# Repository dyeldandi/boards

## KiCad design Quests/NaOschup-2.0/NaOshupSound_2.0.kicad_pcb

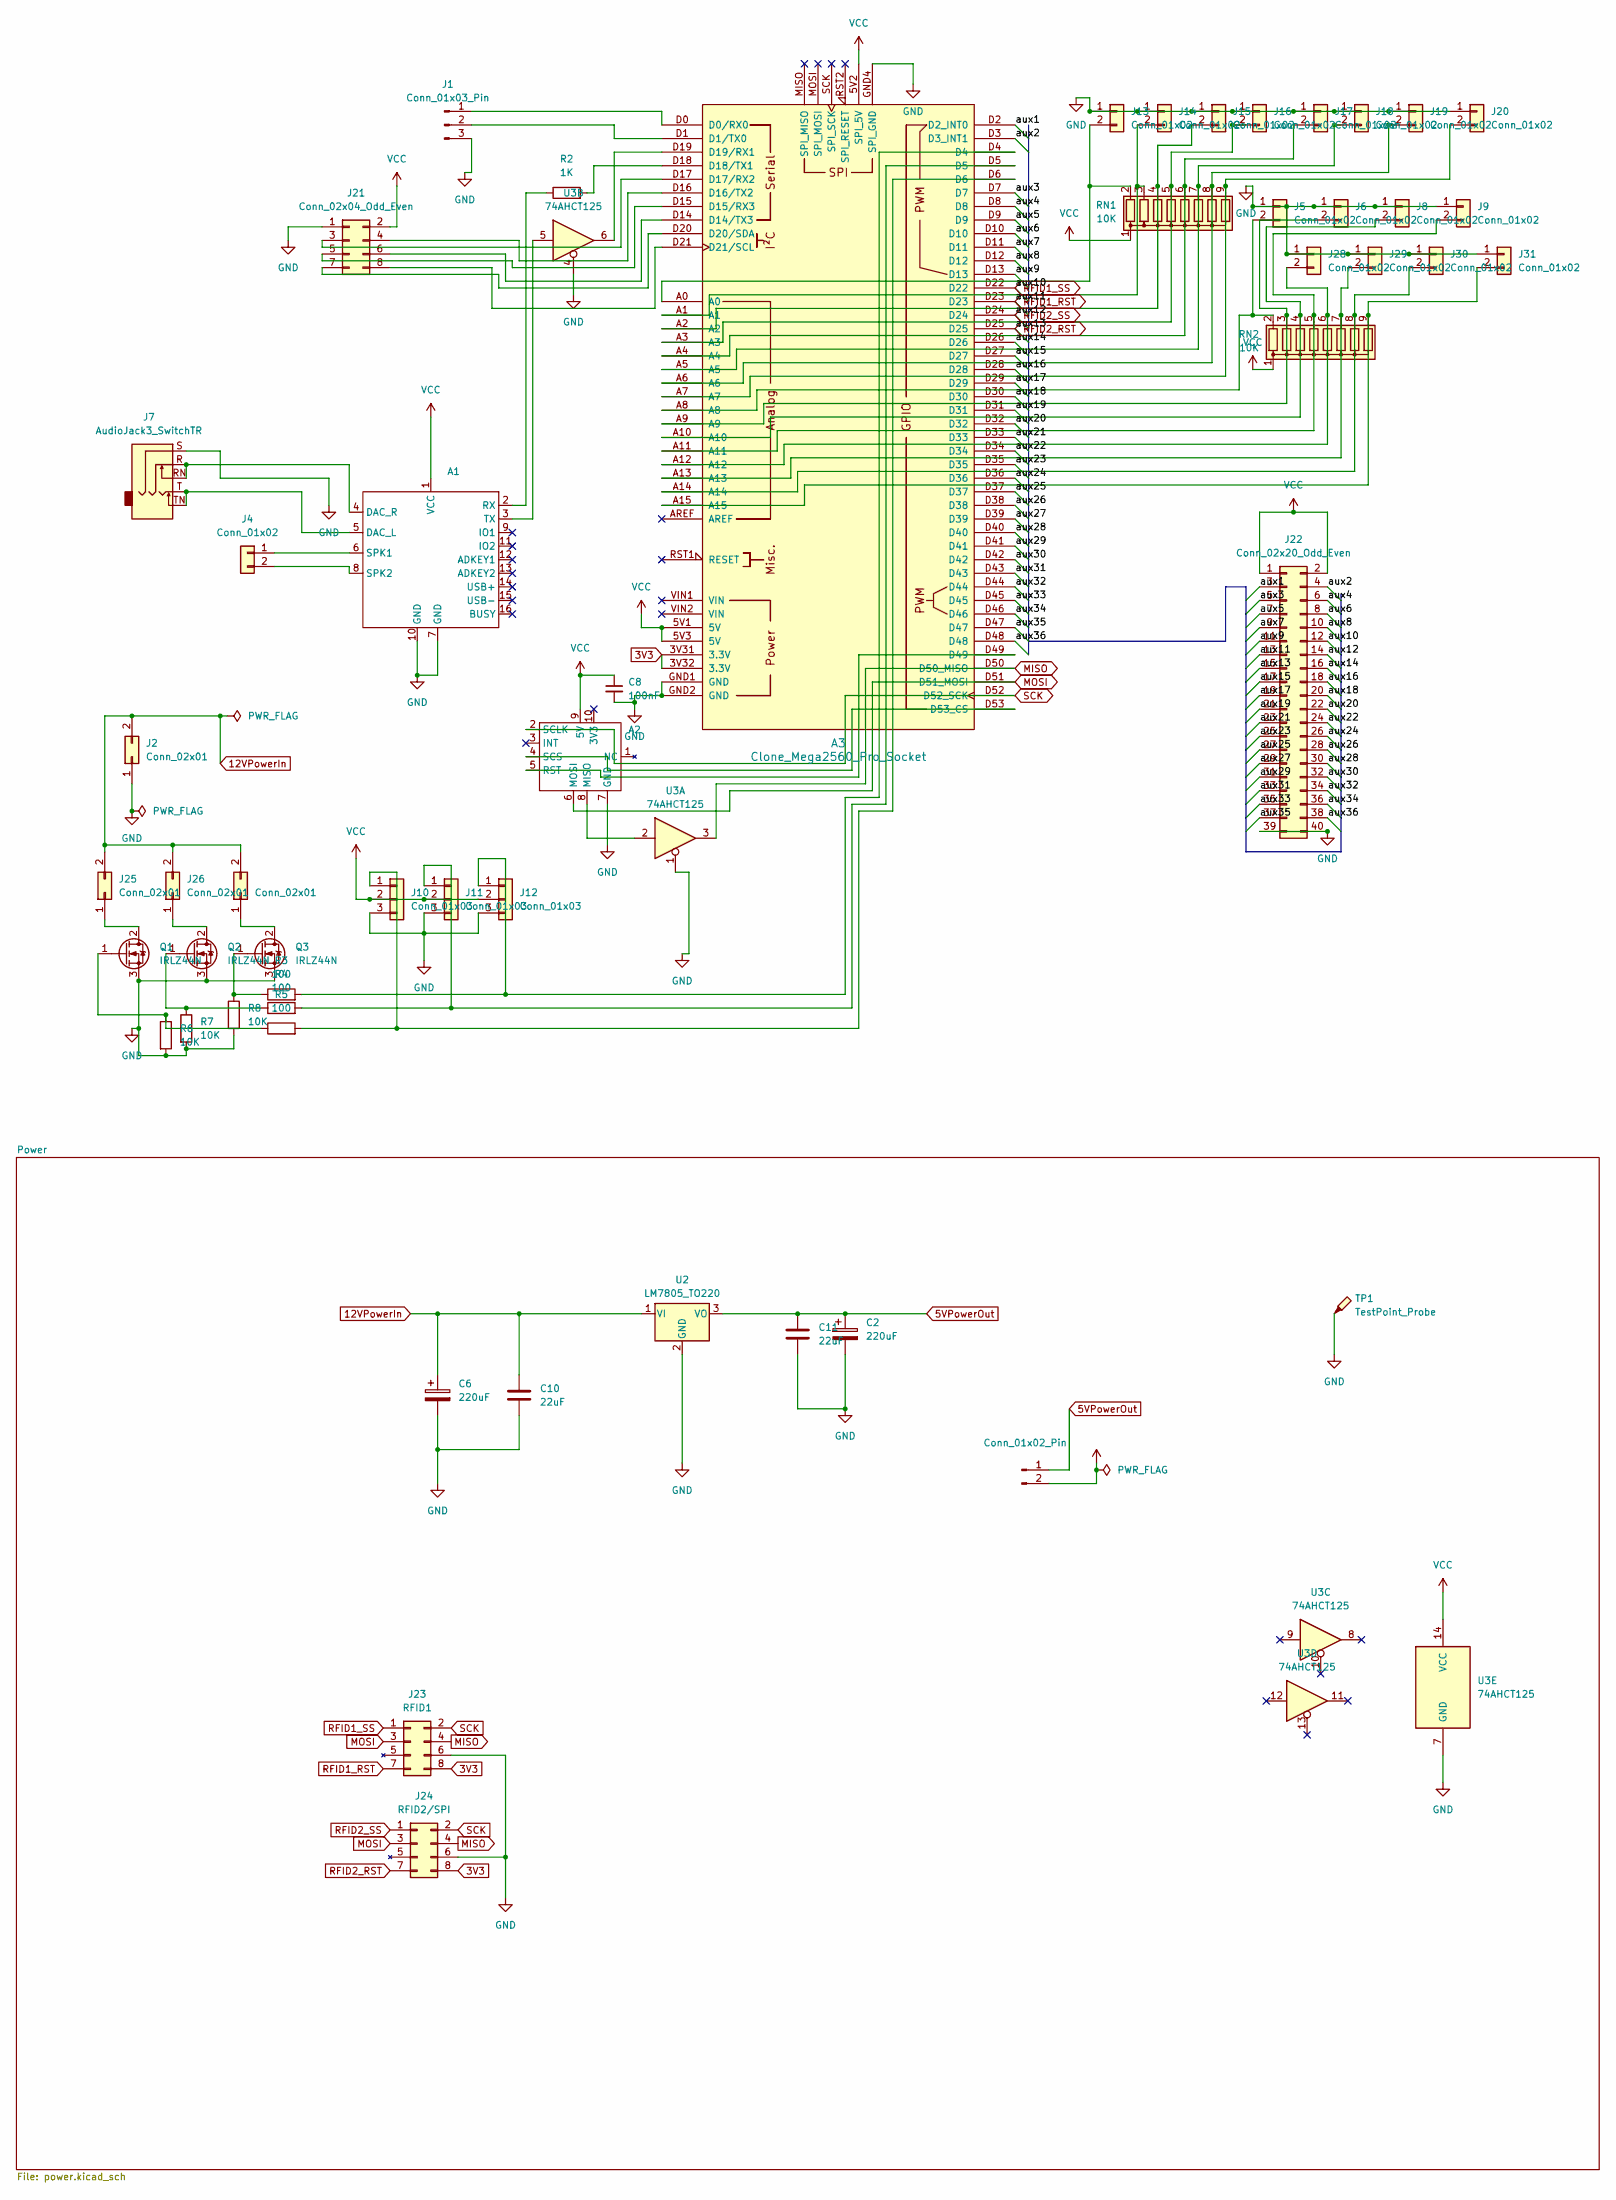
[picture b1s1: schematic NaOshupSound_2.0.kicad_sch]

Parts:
A1: DFPLayerMini
A2: W5500Module
A3: Clone_Mega2560_Pro_Socket
C2, C6: 220uF; CP_Radial_D6.3mm_P2.50mm
C8: 100nF; C_0805_2012Metric_Pad1.18x1.45mm_HandSolder
C10, C11: 22uF; C_1206_3216Metric
J1: Conn_01x03_Pin; FanPinHeader_1x03_P2.54mm_Vertical
J2, J25, J26, J27: Conn_02x01; Molex_Mini-Fit_Jr_5569-02A2_2x01_P4.20mm_Horizontal_Hanging
J3: Conn_01x02_Pin; PinHeader_1x02_P2.54mm_Vertical
J4: Conn_01x02; Connector_Connfly_P2.54_2P
J5, J6, J8, J9, J13, J14, J15, J16, J17, J18, J19, J20, J28, J29, J30, J31: Conn_01x02; Connector_Connfly_P2.54_2P_R
J7: AudioJack3_SwitchTR; Jack_3.5mm_CUI_SJ1-3525N_Horizontal
J10, J11, J12: Conn_01x03; PinSocket_1x03_P2.54mm_Vertical
J21: Conn_02x04_Odd_Even; IDC-Header_2x04_P2.54mm_Vertical
J22: Conn_02x20_Odd_Even; IDC-Header_2x20_P2.54mm_Vertical
J23: RFID1; IDC-Header_2x04_P2.54mm_Vertical
J24: RFID2/SPI; IDC-Header_2x04_P2.54mm_Vertical
Q1, Q2, Q3: IRLZ44N; TO-220-3_Vertical
R2: 1K; R_0805_2012Metric_Pad1.20x1.40mm_HandSolder
R3, R4, R5: 100; R_0805_2012Metric_Pad1.20x1.40mm_HandSolder
R6, R7, R8: 10K; R_0805_2012Metric_Pad1.20x1.40mm_HandSolder
RN1, RN2: 10K; R_Array_SIP9
TP1: TestPoint_Probe; PinHeader_1x01_P2.54mm_Vertical
U2: LM7805_TO220; TO-220-3_Vertical
U3: 74AHCT125; SOIC-14_3.9x8.7mm_P1.27mm

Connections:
3V3: A3.3V31 (3.3V), A3.3V32 (3.3V), J23.8 (VCC_3V3), J24.8 (VCC_3V3)
5VPowerOut: C2.1, C11.1, J3.1, U2.3 (VO)
12VPowerIn: C6.1, C10.1, J2.2, J25.2, J26.2, J27.2, U2.1 (VI)
/aux1: A3.D2 (D2_INT0), J22.3
/aux2: A3.D3 (D3_INT1), J22.4
/aux3: A3.D7, J22.5
/aux4: A3.D8, J22.6
/aux5: A3.D9, J22.7
/aux6: A3.D10, J22.8
/aux7: A3.D11, J22.9
/aux8: A3.D12, J22.10
/aux9: A3.D13, J22.11
/aux14: A3.D26, J22.16
/aux15: A3.D27, J22.17
/aux16: A3.D28, J22.18
/aux17: A3.D29, J22.19
/aux18: A3.D30, J22.20
/aux19: A3.D31, J22.21
/aux20: A3.D32, J22.22
/aux21: A3.D33, J22.23
/aux22: A3.D34, J22.24
/aux23: A3.D35, J22.25
/aux24: A3.D36, J22.26
/aux25: A3.D37, J22.27
/aux26: A3.D38, J22.28
/aux27: A3.D39, J22.29
/aux28: A3.D40, J22.30
/aux29: A3.D41, J22.31
/aux30: A3.D42, J22.32
/aux31: A3.D43, J22.33
/aux32: A3.D44, J22.34
/aux33: A3.D45, J22.35
/aux34: A3.D46, J22.36
/aux35: A3.D47, J22.37
/aux36: A3.D48, J22.38
GND: A1.7 (GND), A1.10 (GND), A2.7 (GND), A3.GND1 (GND), A3.GND2 (GND), A3.GND4 (SPI_GND), C2.2, C6.2, C8.2, C10.2, C11.2, J1.3, J2.1, J5.1, J6.1, J7.S, J8.1, J9.1, J10.3, J11.3, J12.3, J13.1, J14.1, J15.1, J16.1, J17.1, J18.1, J19.1, J20.1, J21.1, J22.39, J22.40, J23.6 (GND), J24.6 (GND), J28.1, J29.1, J30.1, J31.1, Q1.3 (S), Q2.3 (S), Q3.3 (S), R6.2, R7.2, R8.2, TP1.1, U2.2 (GND), U3.1, U3.4, U3.7 (GND)
MISO: A3.D50 (D50_MISO), J23.4 (MISO), J24.4 (MISO), U3.3
MOSI: A2.6 (MOSI), A3.D51 (D51_MOSI), J23.3 (MOSI), J24.3 (MOSI)
unnamed: A1.5 (DAC_L), J7.T, J7.TN
unnamed: A1.4 (DAC_R), J7.R, J7.RN
unnamed: A1.2 (RX), R2.1
unnamed: A1.6 (SPK1), J4.1
unnamed: A1.8 (SPK2), J4.2
unnamed: A1.3 (TX), U3.5
unnamed: A2.8 (MISO), U3.2
unnamed: A2.5 (RST), A3.D49
unnamed: A2.4 (SCS), A3.D53 (D53_CS)
unnamed: A3.D0 (D0/RX0), J1.1
unnamed: A3.D1 (D1/TX0), J1.2
unnamed: A3.D14 (D14/TX3), J21.6
unnamed: A3.D15 (D15/RX3), J21.5
unnamed: A3.D16 (D16/TX2), J21.4
unnamed: A3.D17 (D17/RX2), J21.3
unnamed: A3.D18 (D18/TX1), R2.2
unnamed: A3.D19 (D19/RX1), U3.6
unnamed: A3.D20 (D20/SDA), J21.7
unnamed: A3.D21 (D21/SCL), J21.8
unnamed: A3.A8, J5.2, RN2.2 (R1)
unnamed: A3.A9, J6.2, RN2.3 (R2)
unnamed: A3.A10, J8.2, RN2.4 (R3)
unnamed: A3.A11, J9.2, RN2.5 (R4)
unnamed: A3.D6, J10.1, R5.2
unnamed: A3.D5, J11.1, R4.2
unnamed: A3.D4, J12.1, R3.2
unnamed: A3.A0, J13.2, RN1.2 (R1)
unnamed: A3.A1, J14.2, RN1.3 (R2)
unnamed: A3.A2, J15.2, RN1.4 (R3)
unnamed: A3.A3, J16.2, RN1.5 (R4)
unnamed: A3.A4, J17.2, RN1.6 (R5)
unnamed: A3.A5, J18.2, RN1.7 (R6)
unnamed: A3.A6, J19.2, RN1.8 (R7)
unnamed: A3.A7, J20.2, RN1.9 (R8)
unnamed: J25.1, Q1.2 (D)
unnamed: J26.1, Q2.2 (D)
unnamed: J27.1, Q3.2 (D)
unnamed: A3.A12, J28.2, RN2.6 (R5)
unnamed: A3.A13, J29.2, RN2.7 (R6)
unnamed: A3.A14, J30.2, RN2.8 (R7)
unnamed: A3.A15, J31.2, RN2.9 (R8)
unnamed: Q1.1 (G), R5.1, R6.1
unnamed: Q2.1 (G), R4.1, R7.1
unnamed: Q3.1 (G), R3.1, R8.1
RFID1_RST: A3.D23, J22.13, J23.7 (RST)
RFID1_SS: A3.D22, J22.12, J23.1 (SS)
RFID2_RST: A3.D25, J22.15, J24.7 (RST)
RFID2_SS: A3.D24, J22.14, J24.1 (SS)
SCK: A2.2 (SCLK), A3.D52 (D52_SCK), J23.2 (SCK), J24.2 (SCK)
VCC: A1.1 (VCC), A2.9 (5V), A3.5V1 (5V), A3.5V2 (SPI_5V), A3.5V3 (5V), C8.1, J3.2, J10.2, J11.2, J12.2, J21.2, J22.1, J22.2, RN1.1 (common), RN2.1 (common), U3.14 (VCC)

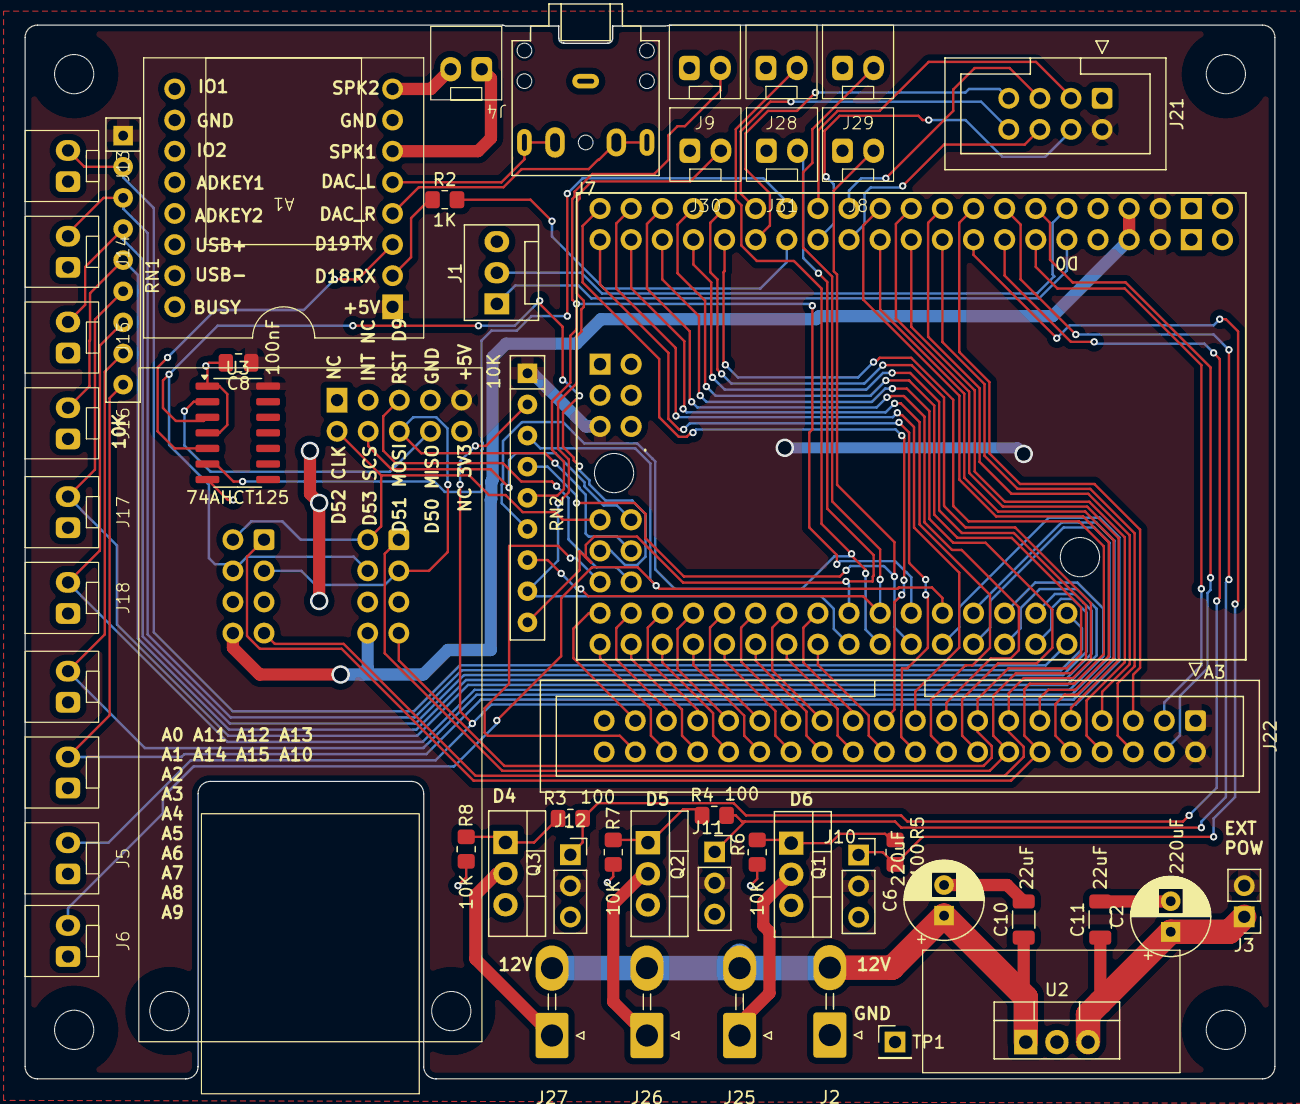
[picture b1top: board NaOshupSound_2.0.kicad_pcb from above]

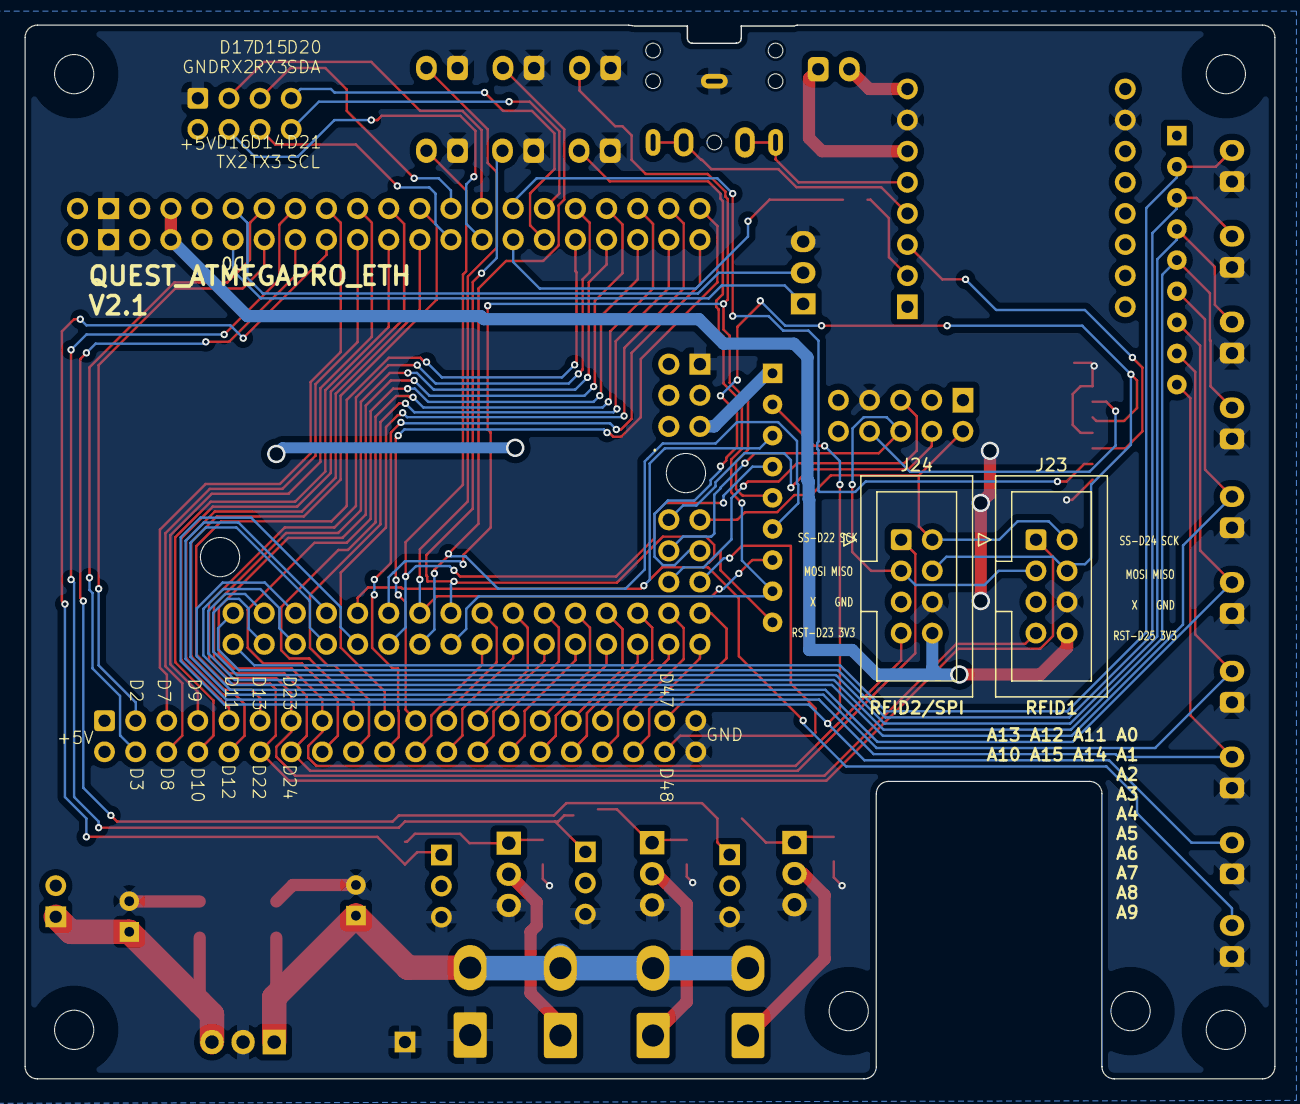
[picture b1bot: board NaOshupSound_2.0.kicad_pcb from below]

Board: 2 copper layers, 102.0 x 86.0 mm, 54 parts (2 on the bottom side), 88 nets.

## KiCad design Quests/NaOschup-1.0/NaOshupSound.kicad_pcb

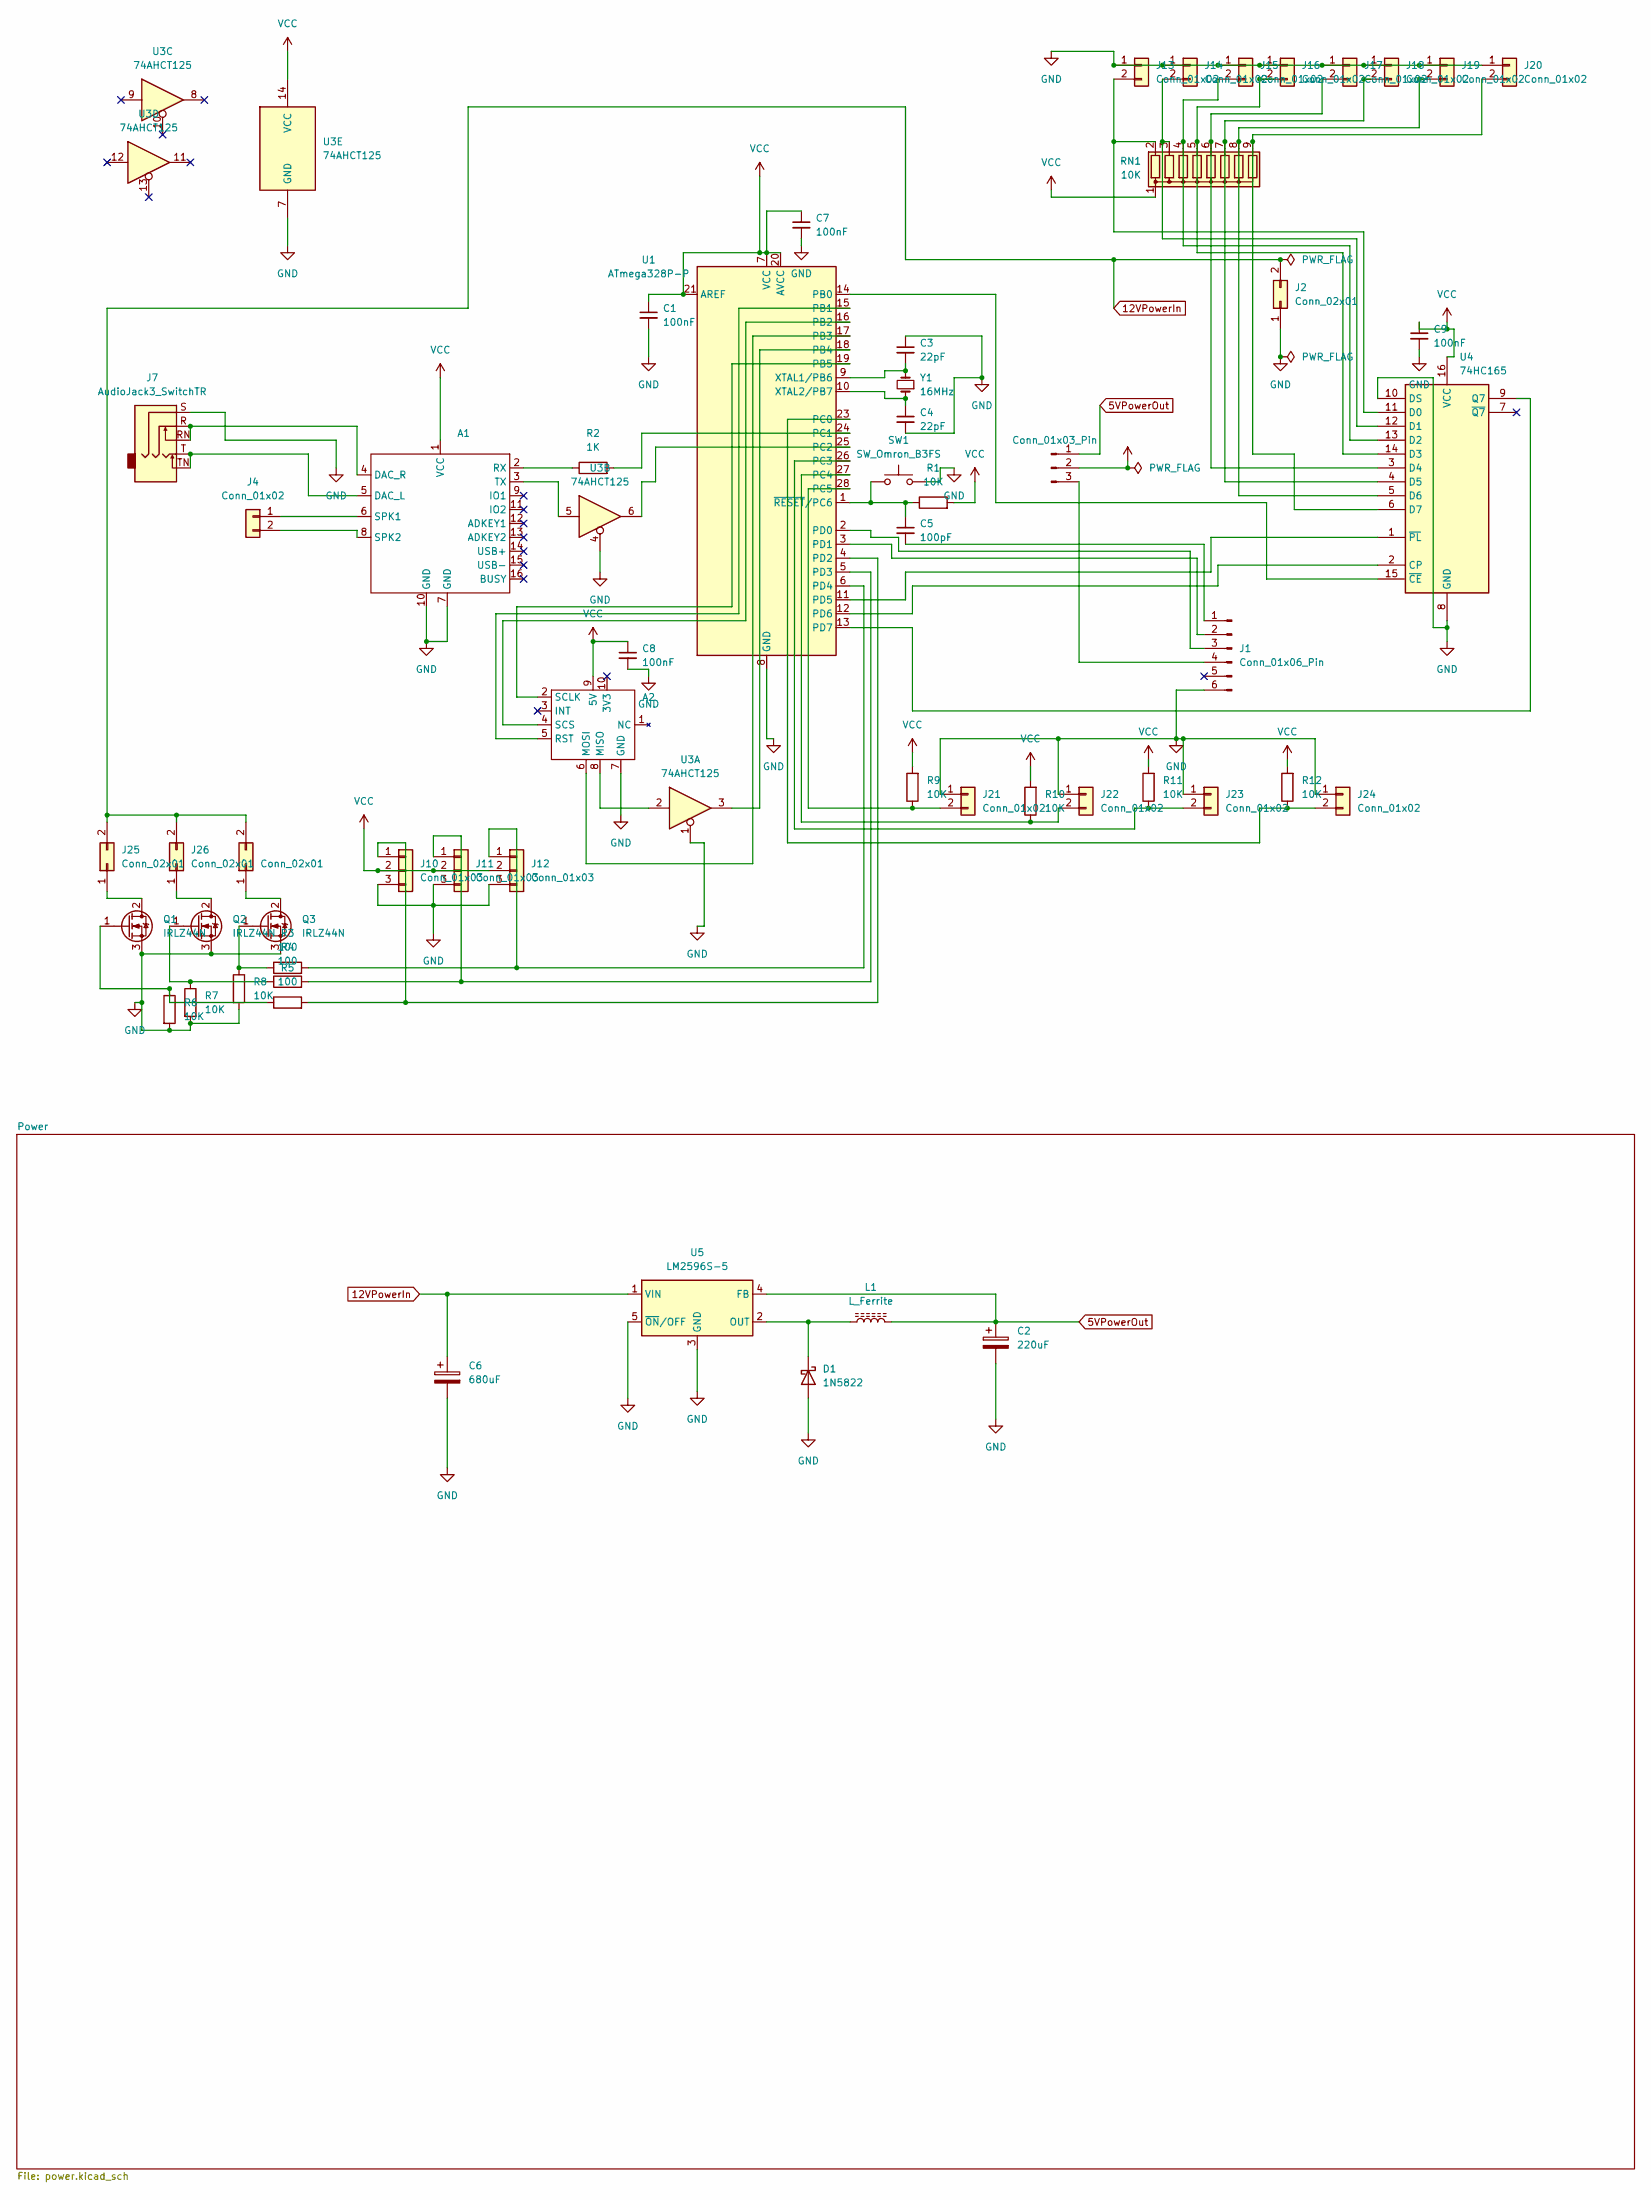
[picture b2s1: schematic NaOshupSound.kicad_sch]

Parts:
A1: DFPLayerMini
A2: W5500Module
C1, C7: 100nF; C_1210_3225Metric
C2: 220uF; CP_Radial_D6.3mm_P2.50mm
C3, C4: 22pF; C_1210_3225Metric
C5: 100pF; C_1210_3225Metric
C6: 680uF; CP_Radial_D6.3mm_P2.50mm
C8, C9: 100nF; C_0805_2012Metric_Pad1.18x1.45mm_HandSolder
D1: 1N5822; D_DO-201AD_P3.81mm_Vertical_AnodeUp
J1: Conn_01x06_Pin; JST_EH_B6B-EH-A_1x06_P2.50mm_Vertical
J2: Conn_02x01; Molex_Mini-Fit_Jr_5569-02A2_2x01_P4.20mm_Horizontal
J3: Conn_01x03_Pin; PinHeader_1x03_P2.54mm_Vertical
J4, J13, J14, J15, J16, J17, J18, J19, J20, J21, J22, J23, J24: Conn_01x02; JST_EH_B2B-EH-A_1x02_P2.50mm_Vertical
J7: AudioJack3_SwitchTR; Jack_3.5mm_CUI_SJ1-3525N_Horizontal
J10, J11, J12: Conn_01x03; PinSocket_1x03_P2.54mm_Vertical
J25, J26, J27: Conn_02x01; Molex_Mini-Fit_Jr_5569-02A2_2x01_P4.20mm_Horizontal_Hanging
L1: L_Ferrite; L_Coilcraft_XAL1510-103
Q1, Q2, Q3: IRLZ44N; TO-220-3_Vertical
R1: 10K; R_1210_3225Metric_Pad1.30x2.65mm_HandSolder
R2: 1K; R_1210_3225Metric_Pad1.30x2.65mm_HandSolder
R3, R4, R5: 100; R_0805_2012Metric_Pad1.20x1.40mm_HandSolder
R6, R7, R8, R9, R10, R11, R12: 10K; R_0805_2012Metric_Pad1.20x1.40mm_HandSolder
RN1: 10K; R_Array_SIP9
SW1: SW_Omron_B3FS; SW_SPST_Omron_B3FS-100xP
U1: ATmega328P-P; DIP-28_W7.62mm
U3: 74AHCT125; SOIC-14_3.9x8.7mm_P1.27mm
U4: 74HC165; SOIC-16_3.9x9.9mm_P1.27mm
U5: LM2596S-5; TO-263-5_TabPin3
Y1: 16MHz; Crystal_HC49-U_Vertical

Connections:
5VPowerOut: C2.1, J3.1, L1.2, U5.4 (FB)
12VPowerIn: C6.1, J2.2, J25.2, J26.2, J27.2, U5.1 (VIN)
GND: A1.7 (GND), A1.10 (GND), A2.7 (GND), C1.2, C2.2, C3.1, C4.2, C6.2, C7.2, C8.2, C9.2, D1.2 (A), J1.6, J2.1, J7.S, J10.3, J11.3, J12.3, J13.1, J14.1, J15.1, J16.1, J17.1, J18.1, J19.1, J20.1, J21.1, J22.1, J23.1, J24.1, Q1.3 (S), Q2.3 (S), Q3.3 (S), R6.2, R7.2, R8.2, SW1.2, U1.8 (GND), U1.22 (GND), U3.1, U3.4, U3.7 (GND), U4.8 (GND), U4.10 (DS), U5.3 (GND), U5.5 (~ON/OFF)
unnamed: A1.5 (DAC_L), J7.T, J7.TN
unnamed: A1.4 (DAC_R), J7.R, J7.RN
unnamed: A1.2 (RX), R2.1
unnamed: A1.6 (SPK1), J4.1
unnamed: A1.8 (SPK2), J4.2
unnamed: A1.3 (TX), U3.5
unnamed: A2.8 (MISO), U3.2
unnamed: A2.6 (MOSI), U1.17 (PB3)
unnamed: A2.5 (RST), U1.15 (PB1)
unnamed: A2.2 (SCLK), U1.19 (PB5)
unnamed: A2.4 (SCS), U1.16 (PB2)
unnamed: D1.1 (K), L1.1, U5.2 (OUT)
unnamed: C5.2, J1.1
unnamed: J1.2, U1.3 (PD1)
unnamed: J1.3, U1.2 (PD0)
unnamed: J1.4, J3.3
unnamed: J10.1, R5.2, U1.4 (PD2)
unnamed: J11.1, R4.2, U1.5 (PD3)
unnamed: J12.1, R3.2, U1.6 (PD4)
unnamed: J13.2, RN1.2 (R1), U4.11 (D0)
unnamed: J14.2, RN1.3 (R2), U4.12 (D1)
unnamed: J15.2, RN1.4 (R3), U4.13 (D2)
unnamed: J16.2, RN1.5 (R4), U4.14 (D3)
unnamed: J17.2, RN1.6 (R5), U4.3 (D4)
unnamed: J18.2, RN1.7 (R6), U4.4 (D5)
unnamed: J19.2, RN1.8 (R7), U4.5 (D6)
unnamed: J20.2, RN1.9 (R8), U4.6 (D7)
unnamed: J21.2, R9.1, U1.28 (PC5)
unnamed: J22.2, R10.1, U1.27 (PC4)
unnamed: J23.2, R11.1, U1.26 (PC3)
unnamed: J24.2, R12.1, U1.23 (PC0)
unnamed: J25.1, Q1.2 (D)
unnamed: J26.1, Q2.2 (D)
unnamed: J27.1, Q3.2 (D)
unnamed: Q1.1 (G), R5.1, R6.1
unnamed: Q2.1 (G), R4.1, R7.1
unnamed: Q3.1 (G), R3.1, R8.1
unnamed: U1.14 (PB0), U4.15 (~CE)
unnamed: U1.18 (PB4), U3.3
unnamed: R2.2, U1.24 (PC1)
unnamed: U1.25 (PC2), U3.6
unnamed: U1.11 (PD5), U4.1 (~PL)
unnamed: U1.12 (PD6), U4.2 (CP)
unnamed: U1.13 (PD7), U4.9 (Q7)
unnamed: C3.2, U1.9 (XTAL1/PB6), Y1.2
unnamed: C4.1, U1.10 (XTAL2/PB7), Y1.1
unnamed: C5.1, R1.1, SW1.1, U1.1 (~RESET/PC6)
VCC: A1.1 (VCC), A2.9 (5V), C1.1, C7.1, C8.1, C9.1, J3.2, J10.2, J11.2, J12.2, R1.2, R9.2, R10.2, R11.2, R12.2, RN1.1 (common), U1.7 (VCC), U1.20 (AVCC), U1.21 (AREF), U3.14 (VCC), U4.16 (VCC)

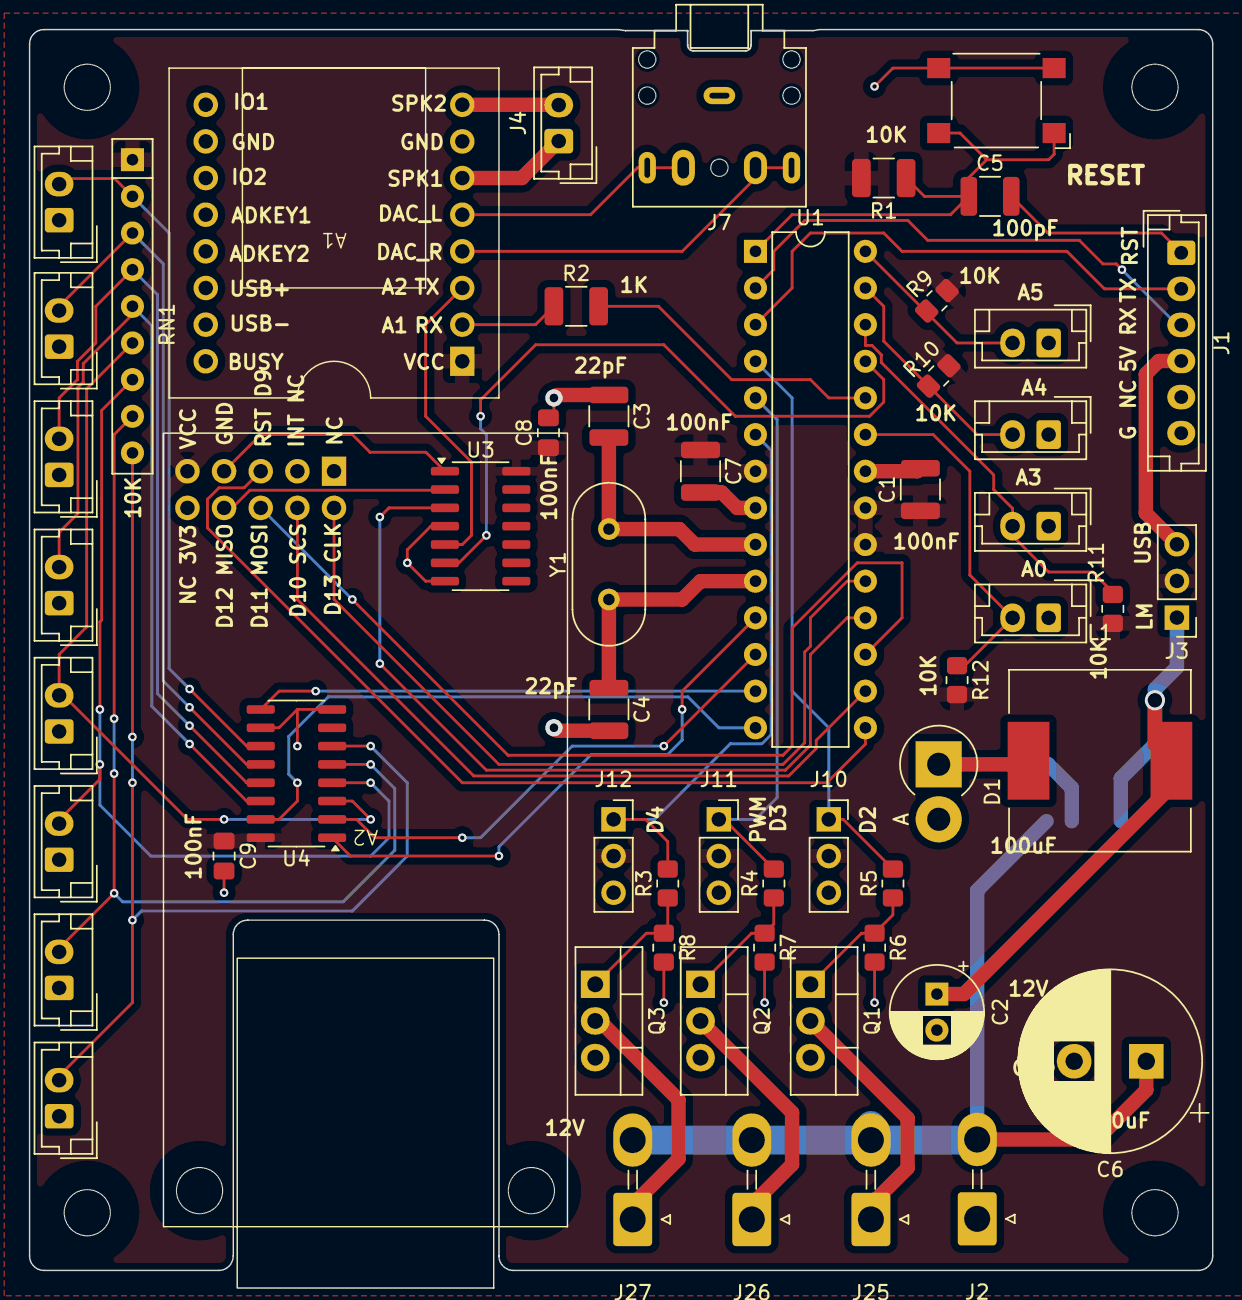
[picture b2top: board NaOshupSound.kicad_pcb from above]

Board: 2 copper layers, 82.0 x 86.0 mm, 58 parts (1 on the bottom side), 51 nets.

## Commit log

2025-02-13 NaOshup boards
2025-02-13 libs
2025-03-19 rfid
